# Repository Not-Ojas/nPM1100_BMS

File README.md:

**BMS using nPM1100**

A nPM1100 based Battery Management System

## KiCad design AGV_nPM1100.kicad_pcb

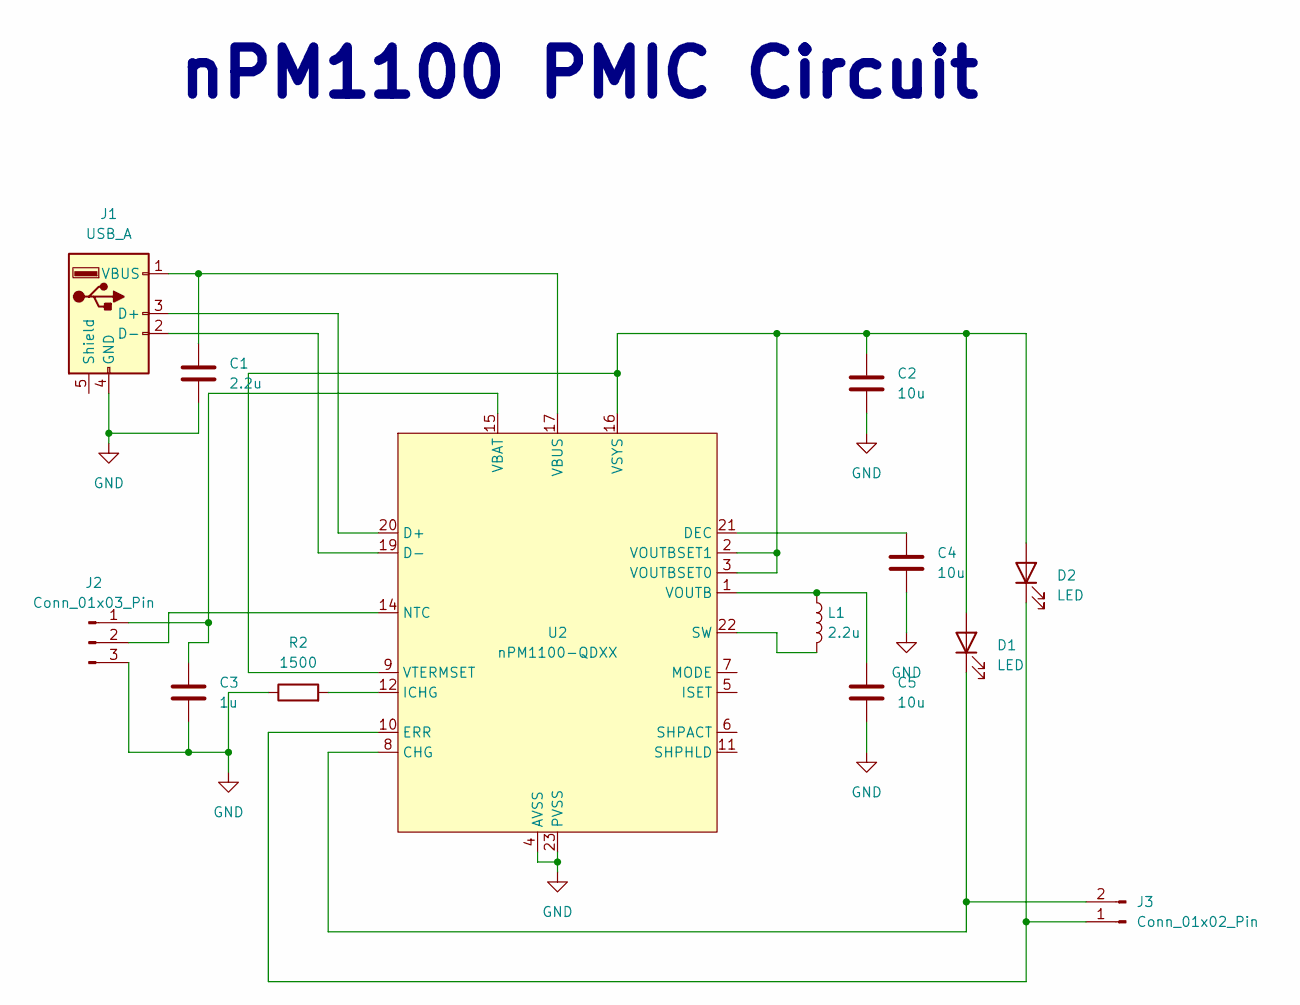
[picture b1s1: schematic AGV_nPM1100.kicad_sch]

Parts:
C1: 2.2u; C_0603_1608Metric
C2, C4, C5: 10u; C_0603_1608Metric
C3: 1u; C_0603_1608Metric
D1, D2: LED; LED_0603_1608Metric
J1: USB_A; USB_A_CNCTech_1001-011-01101_Horizontal
J2: Conn_01x03_Pin; PinHeader_1x03_P2.54mm_Vertical
J3: Conn_01x02_Pin; PinHeader_1x02_P2.54mm_Vertical
L1: 2.2u; L_0603_1608Metric
R2: 1500; R_0603_1608Metric
U2: nPM1100-QDXX; QFN24_NPM1100_NOR

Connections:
GND: C1.2, C2.2, C3.2, C4.2, C5.2, J1.4 (GND), J2.3, R2.1, U2.4 (AVSS), U2.23 (PVSS), U2.25 (AVSS)
unnamed: C2.1, D1.2 (A), D2.2 (A), U2.2 (VOUTBSET1), U2.3 (VOUTBSET0), U2.9 (VTERMSET), U2.16 (VSYS)
unnamed: D1.1 (K), J3.2, U2.8 (CHG)
unnamed: D2.1 (K), J3.1, U2.10 (ERR)
unnamed: J1.3 (D+), U2.20 (D+)
unnamed: J1.2 (D-), U2.19 (D-)
unnamed: C1.1, J1.1 (VBUS), U2.17 (VBUS)
unnamed: C3.1, J2.1, U2.15 (VBAT)
unnamed: J2.2, U2.14 (NTC)
unnamed: C4.1, U2.21 (DEC)
unnamed: R2.2, U2.12 (ICHG)
unnamed: L1.2, U2.22 (SW)
unnamed: C5.1, L1.1, U2.1 (VOUTB)

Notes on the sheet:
nPM1100 PMIC Circuit

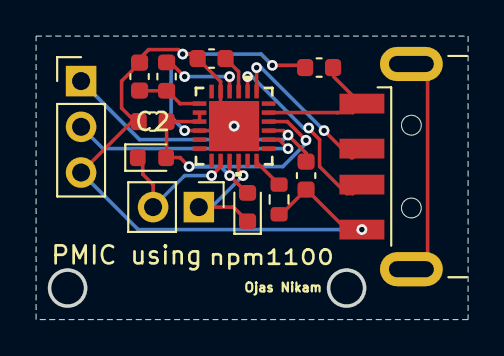
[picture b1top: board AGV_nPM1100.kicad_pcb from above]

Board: 2 copper layers, 23.8 x 15.6 mm, 13 parts (0 on the bottom side), 13 nets.
